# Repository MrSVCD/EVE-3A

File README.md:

# EVE-3A
EVE-3A is a project to make a ADM-3A compatible terminal in a keyboard.

So far MrSVCD has competed a first draft of a Ortholinear and a ADM-3A (Original Layout) inspired keyboard layout.

## Keyboard
### Ortholinear
Renders of the first draft

### ADM-3A inspired (Original Layout)
Renders of the first draft

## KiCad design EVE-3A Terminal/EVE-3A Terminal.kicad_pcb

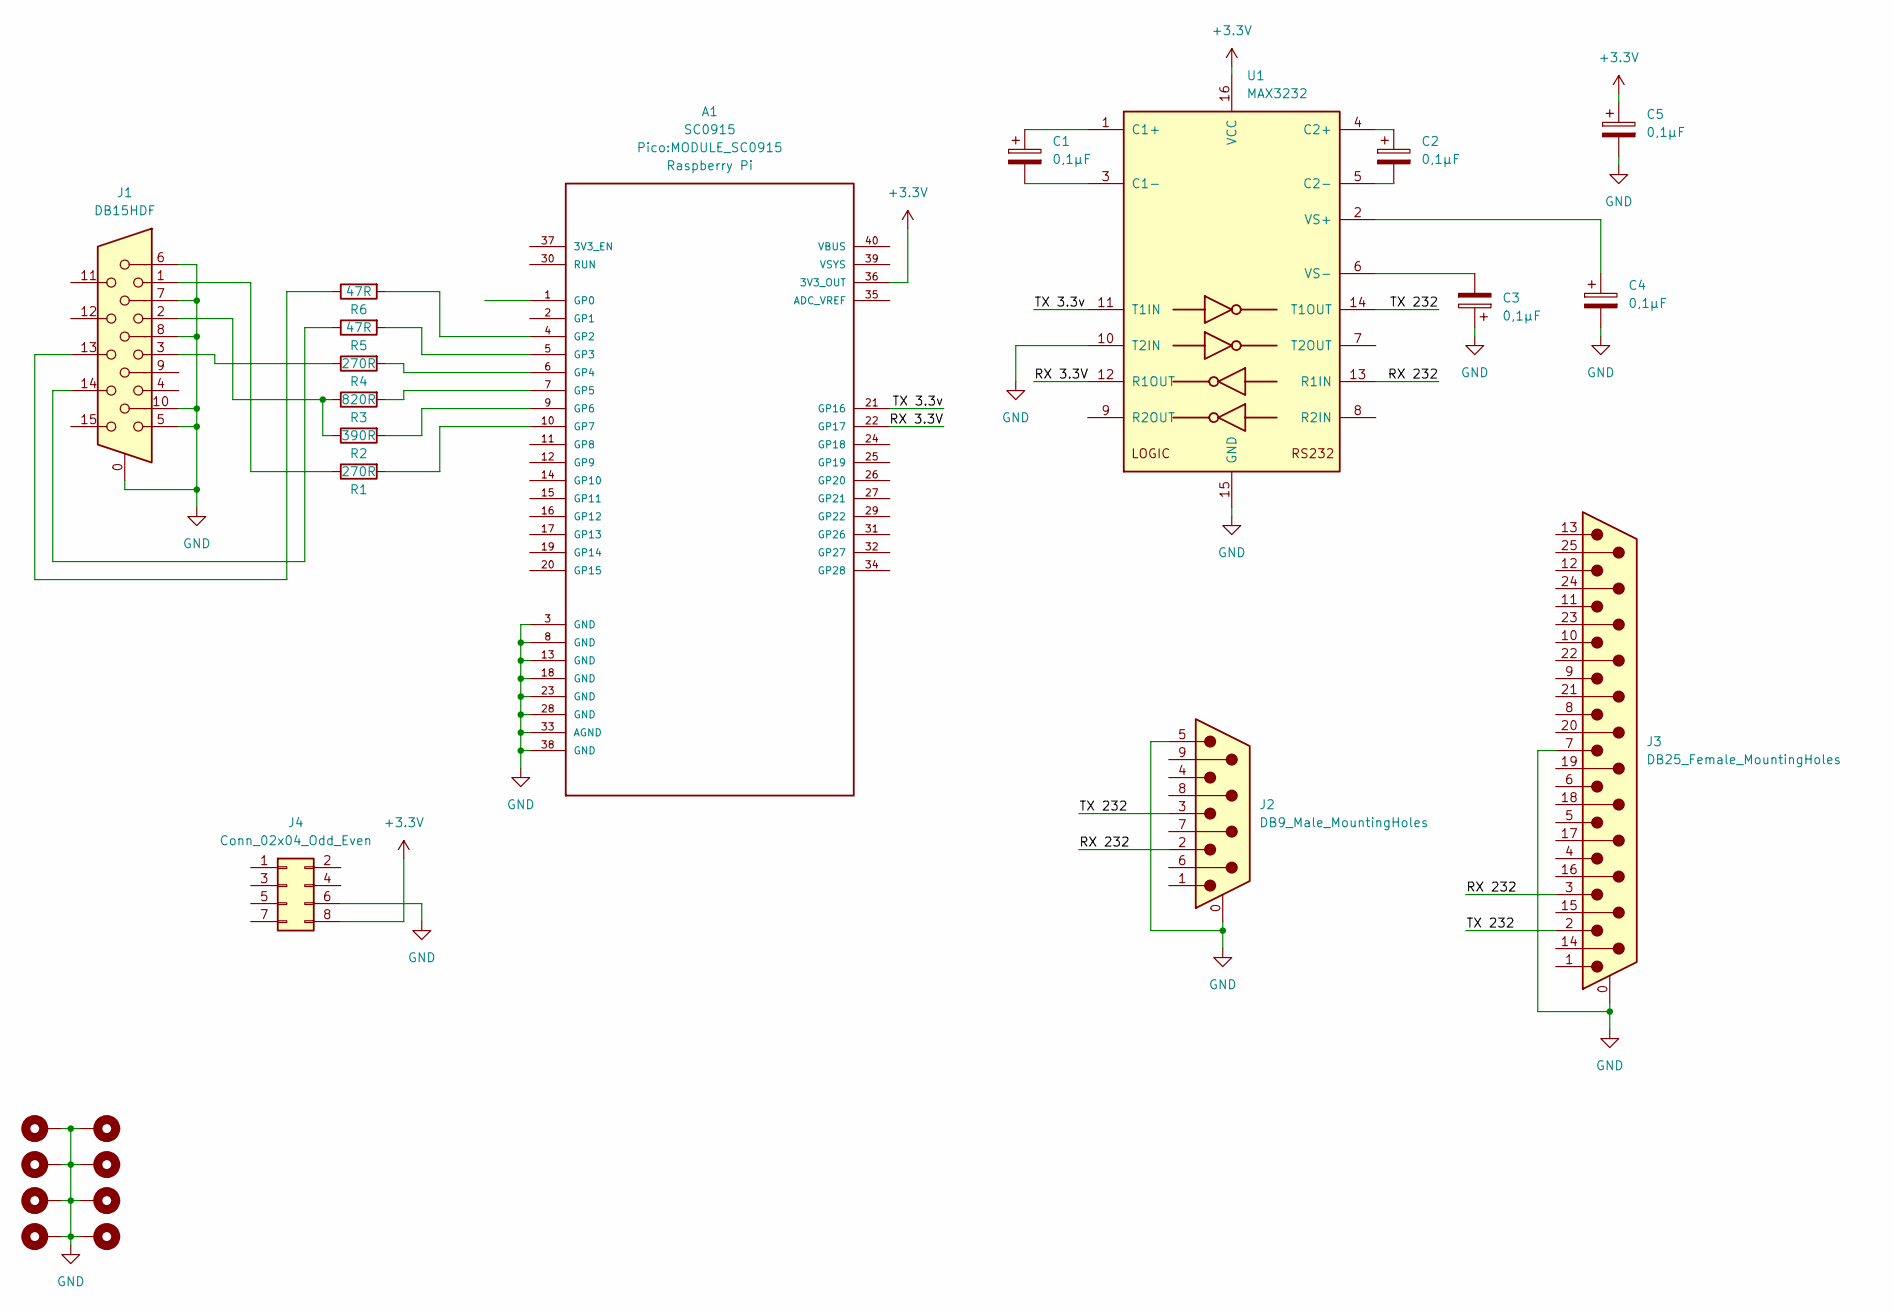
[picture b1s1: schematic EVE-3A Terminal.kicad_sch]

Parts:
A1: SC0915; MODULE_SC0915; PARTREV 1.6
C1, C2, C3, C4, C5: 0,1µF; CP_Radial_D5.0mm_P2.50mm
H1, H2, H3, H4, H5, H6, H7, H8: MountingHole_Pad; MountingHole_3.2mm_M3_Pad_Via
J1: DB15HDF; DSUB-15-HD_Female_Horizontal_P2.29x1.98mm_EdgePinOffset3.03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
J2: DB9_Male_MountingHoles; DSUB-9_Male_Horizontal_P2.77x2.84mm_EdgePinOffset4.94mm_Hou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
J3: DB25_Female_MountingHoles; DSUB-25_Male_Horizontal_P2.77x2.84mm_EdgePinOffset4.94mm_Ho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
J4: Conn_02x04_Odd_Even; PinSocket_2x04_P2.54mm_Vertical
R1, R4: 270R; R_Axial_DIN0207_L6.3mm_D2.5mm_P7.62mm_Horizontal
R2: 390R; R_Axial_DIN0207_L6.3mm_D2.5mm_P7.62mm_Horizontal
R3: 820R; R_Axial_DIN0207_L6.3mm_D2.5mm_P7.62mm_Horizontal
R5, R6: 47R; R_Axial_DIN0207_L6.3mm_D2.5mm_P7.62mm_Horizontal
U1: MAX3232; DIP-16_W7.62mm_Socket_LongPads

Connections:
+3.3V: A1.36 (3V3_OUT), C5.1, J4.8, U1.16 (VCC)
/RX 3.3V: A1.22 (GP17), U1.12 (R1OUT)
/RX 232: J2.2, J3.3, U1.13 (R1IN)
/TX 3.3v: A1.21 (GP16), U1.11 (T1IN)
/TX 232: J2.3, J3.2, U1.14 (T1OUT)
GND: A1.3 (GND), A1.8 (GND), A1.13 (GND), A1.18 (GND), A1.23 (GND), A1.28 (GND), A1.33 (AGND), A1.38 (GND), C3.1, C4.2, C5.2, H1.1, H2.1, H3.1, H4.1, H5.1, H6.1, H7.1, H8.1, J1.0, J1.5, J1.6, J1.7, J1.8, J1.10, J2.0 (PAD), J2.5, J3.0 (PAD), J3.7, J4.6, U1.10 (T2IN), U1.15 (GND)
unnamed: A1.4 (GP2), R6.2
unnamed: A1.5 (GP3), R5.2
unnamed: A1.6 (GP4), R4.2
unnamed: A1.7 (GP5), R3.2
unnamed: A1.9 (GP6), R2.2
unnamed: A1.10 (GP7), R1.2
unnamed: C1.1, U1.1 (C1+)
unnamed: C1.2, U1.3 (C1-)
unnamed: C2.1, U1.4 (C2+)
unnamed: C2.2, U1.5 (C2-)
unnamed: C3.2, U1.6 (VS-)
unnamed: C4.1, U1.2 (VS+)
unnamed: J1.1, R1.1
unnamed: J1.2, R2.1, R3.1
unnamed: J1.3, R4.1
unnamed: J1.13, R6.1
unnamed: J1.14, R5.1

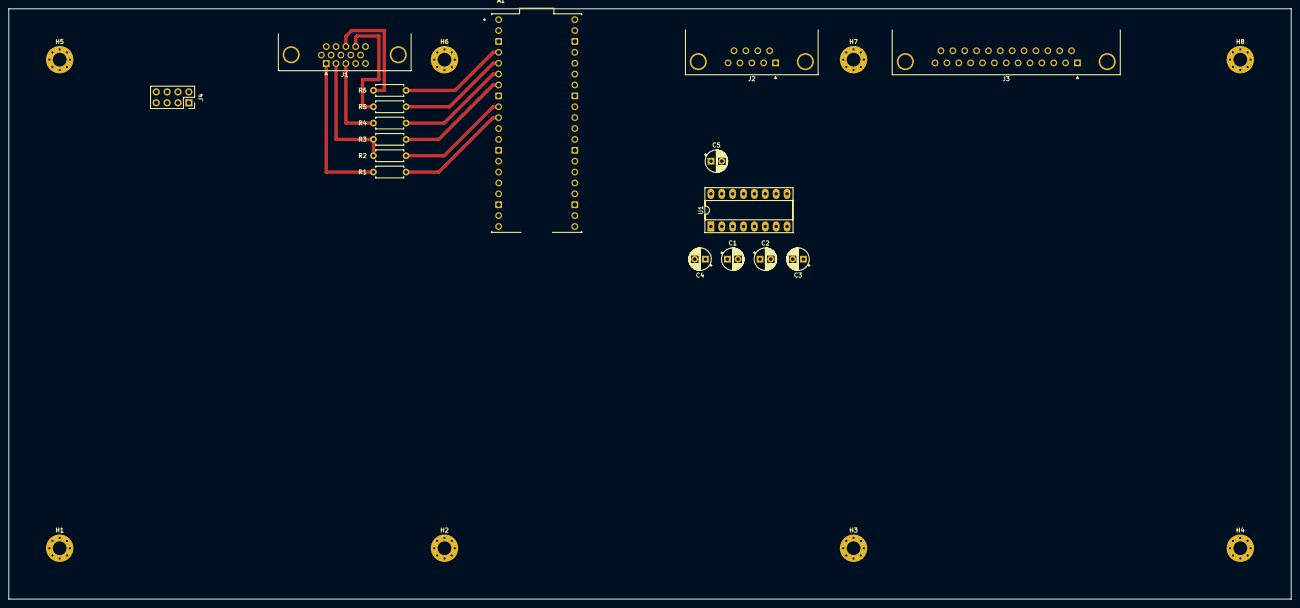
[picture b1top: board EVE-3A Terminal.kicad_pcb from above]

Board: 2 copper layers, 299.2 x 137.8 mm, 25 parts (0 on the bottom side), 23 nets.

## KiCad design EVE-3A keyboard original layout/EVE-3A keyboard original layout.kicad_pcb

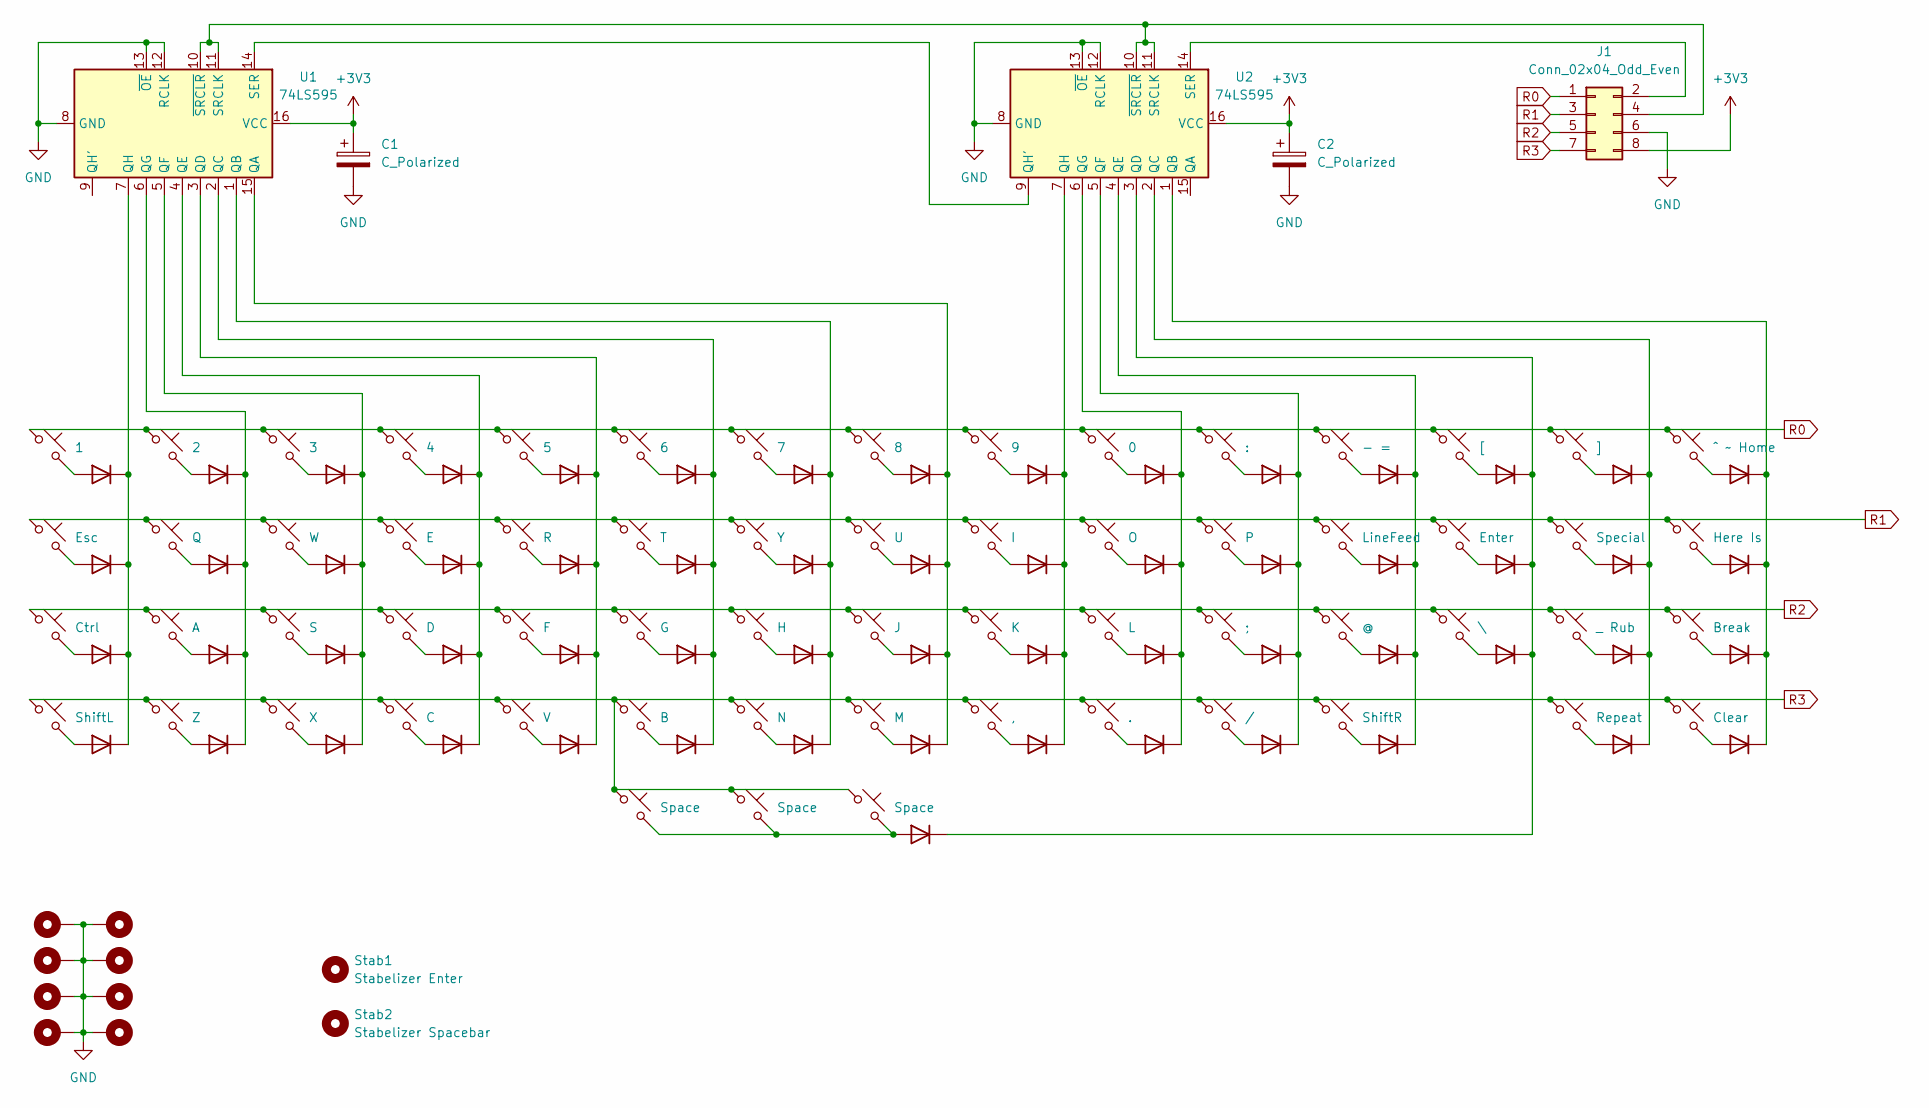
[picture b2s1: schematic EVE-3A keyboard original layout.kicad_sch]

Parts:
C1, C2: C_Polarized; CP_Radial_D7.5mm_P2.50mm
D1, D2, D3, D4, D5, D6, D7, D8, D9, D10, D11, D12, D13, D14, D15, D16, D17, D18, D19, D20, D21, D22, D23, D24, D25, D26, D27, D28, D29, D30, D31, D32, D33, D34, D35, D36, D37, D38, D39, D40, D41, D42, D43, D44, D45, D46, D47, D48, D49, D50, D51, D52, D53, D54, D55, D56, D57, D58, D59, D60: 1N4148; D_DO-35_SOD27_P7.62mm_Horizontal
H1, H2, H3, H4, H5, H6, H7, H8: MountingHole_Pad; MountingHole_3.2mm_M3_Pad_Via
J1: Conn_02x04_Odd_Even; IDC-Header_2x04_P2.54mm_Vertical
SW1: 1; SW_Hybrid_Cherry_MX_Alps_1.00u
SW2: Esc; SW_Hybrid_Cherry_MX_Alps_1.00u
SW3: Ctrl; SW_Hybrid_Cherry_MX_Alps_1.00u
SW4: ShiftL; SW_Hybrid_Cherry_MX_Alps_1.50u
SW5: 2; SW_Hybrid_Cherry_MX_Alps_1.00u
SW6: Q; SW_Hybrid_Cherry_MX_Alps_1.00u
SW7: A; SW_Hybrid_Cherry_MX_Alps_1.00u
SW8: Z; SW_Hybrid_Cherry_MX_Alps_1.00u
SW9: 3; SW_Hybrid_Cherry_MX_Alps_1.00u
SW10: W; SW_Hybrid_Cherry_MX_Alps_1.00u
SW11: S; SW_Hybrid_Cherry_MX_Alps_1.00u
SW12: X; SW_Hybrid_Cherry_MX_Alps_1.00u
SW13: 4; SW_Hybrid_Cherry_MX_Alps_1.00u
SW14: E; SW_Hybrid_Cherry_MX_Alps_1.00u
SW15: D; SW_Hybrid_Cherry_MX_Alps_1.00u
SW16: C; SW_Hybrid_Cherry_MX_Alps_1.00u
SW17: 5; SW_Hybrid_Cherry_MX_Alps_1.00u
SW18: R; SW_Hybrid_Cherry_MX_Alps_1.00u
SW19: F; SW_Hybrid_Cherry_MX_Alps_1.00u
SW20: V; SW_Hybrid_Cherry_MX_Alps_1.00u
SW21: 6; SW_Hybrid_Cherry_MX_Alps_1.00u
SW22: T; SW_Hybrid_Cherry_MX_Alps_1.00u
SW23: G; SW_Hybrid_Cherry_MX_Alps_1.00u
SW24: B; SW_Hybrid_Cherry_MX_Alps_1.00u
SW25, SW35: Space; SW_Hybrid_Cherry_MX_Alps_1.50u
SW26: 7; SW_Hybrid_Cherry_MX_Alps_1.00u
SW27: Y; SW_Hybrid_Cherry_MX_Alps_1.00u
SW28: H; SW_Hybrid_Cherry_MX_Alps_1.00u
SW29: N; SW_Hybrid_Cherry_MX_Alps_1.00u
SW30: Space; SW_Hybrid_Cherry_MX_Alps_6.50u
SW31: 8; SW_Hybrid_Cherry_MX_Alps_1.00u
SW32: U; SW_Hybrid_Cherry_MX_Alps_1.00u
SW33: J; SW_Hybrid_Cherry_MX_Alps_1.00u
SW34: M; SW_Hybrid_Cherry_MX_Alps_1.00u
SW36: 9; SW_Hybrid_Cherry_MX_Alps_1.00u
SW37: I; SW_Hybrid_Cherry_MX_Alps_1.00u
SW38: K; SW_Hybrid_Cherry_MX_Alps_1.00u
SW39: ,; SW_Hybrid_Cherry_MX_Alps_1.00u
SW40: 0; SW_Hybrid_Cherry_MX_Alps_1.00u
SW41: O; SW_Hybrid_Cherry_MX_Alps_1.00u
SW42: L; SW_Hybrid_Cherry_MX_Alps_1.00u
SW43: .; SW_Hybrid_Cherry_MX_Alps_1.00u
SW44: :; SW_Hybrid_Cherry_MX_Alps_1.00u
SW45: P; SW_Hybrid_Cherry_MX_Alps_1.00u
SW46: ;; SW_Hybrid_Cherry_MX_Alps_1.00u
SW47: /; SW_Hybrid_Cherry_MX_Alps_1.00u
SW48: - =; SW_Hybrid_Cherry_MX_Alps_1.00u
SW49: LineFeed; SW_Hybrid_Cherry_MX_Alps_1.00u
SW50: @; SW_Hybrid_Cherry_MX_Alps_1.00u
SW51: ShiftR; SW_Hybrid_Cherry_MX_Alps_1.50u
SW52: [; SW_Hybrid_Cherry_MX_Alps_1.00u
SW53: Enter; SW_Hybrid_Cherry_MX_Alps_2.00u
SW54: \; SW_Hybrid_Cherry_MX_Alps_1.00u
SW55: ]; SW_Hybrid_Cherry_MX_Alps_1.00u
SW56: _ Rub; SW_Hybrid_Cherry_MX_Alps_1.00u
SW57: Repeat; SW_Hybrid_Cherry_MX_Alps_1.00u
SW58: ^ ~ Home; SW_Hybrid_Cherry_MX_Alps_1.00u
SW59: Here Is; SW_Hybrid_Cherry_MX_Alps_1.00u
SW60: Break; SW_Hybrid_Cherry_MX_Alps_1.00u
SW61: Clear; SW_Hybrid_Cherry_MX_Alps_1.00u
SW62: Special; SW_PUSH-12mm
Stab1: Stabelizer Enter; Stabilizer_Cherry_MX_2.00u
Stab2: Stabelizer Spacebar; Stabilizer_Cherry_MX_6.00u
U1, U2: 74LS595; DIP-16_W7.62mm_Socket

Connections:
+3V3: C1.1, C2.1, J1.8, U1.16 (VCC), U2.16 (VCC)
GND: C1.2, C2.2, H1.1, H2.1, H3.1, H4.1, H5.1, H6.1, H7.1, H8.1, J1.6, U1.8 (GND), U1.12 (RCLK), U1.13 (~OE), U2.8 (GND), U2.12 (RCLK), U2.13 (~OE)
unnamed: D1.1 (K), D2.1 (K), D3.1 (K), D4.1 (K), U1.7 (QH)
unnamed: D1.2 (A), SW1.1
unnamed: D2.2 (A), SW2.1
unnamed: D3.2 (A), SW3.1
unnamed: D4.2 (A), SW4.1
unnamed: D5.1 (K), D6.1 (K), D7.1 (K), D8.1 (K), U1.6 (QG)
unnamed: D5.2 (A), SW5.1
unnamed: D6.2 (A), SW6.1
unnamed: D7.2 (A), SW7.1
unnamed: D8.2 (A), SW8.1
unnamed: D9.2 (A), SW9.1
unnamed: D9.1 (K), D10.1 (K), D11.1 (K), D12.1 (K), U1.5 (QF)
unnamed: D10.2 (A), SW10.1
unnamed: D11.2 (A), SW11.1
unnamed: D12.2 (A), SW12.1
unnamed: D13.1 (K), D14.1 (K), D15.1 (K), D16.1 (K), U1.4 (QE)
unnamed: D13.2 (A), SW13.1
unnamed: D14.2 (A), SW14.1
unnamed: D15.2 (A), SW15.1
unnamed: D16.2 (A), SW16.1
unnamed: D17.1 (K), D18.1 (K), D19.1 (K), D20.1 (K), U1.3 (QD)
unnamed: D17.2 (A), SW17.1
unnamed: D18.2 (A), SW18.1
unnamed: D19.2 (A), SW19.1
unnamed: D20.2 (A), SW20.1
unnamed: D21.1 (K), D22.1 (K), D23.1 (K), D24.1 (K), U1.2 (QC)
unnamed: D21.2 (A), SW21.1
unnamed: D22.2 (A), SW22.1
unnamed: D23.2 (A), SW23.1
unnamed: D24.2 (A), SW24.1
unnamed: D25.1 (K), D26.1 (K), D27.1 (K), D28.1 (K), U1.1 (QB)
unnamed: D25.2 (A), SW26.1
unnamed: D26.2 (A), SW27.1
unnamed: D27.2 (A), SW28.1
unnamed: D28.2 (A), SW29.1
unnamed: D29.1 (K), D30.1 (K), D31.1 (K), D32.1 (K), U1.15 (QA)
unnamed: D29.2 (A), SW31.1
unnamed: D30.2 (A), SW32.1
unnamed: D31.2 (A), SW33.1
unnamed: D32.2 (A), SW34.1
unnamed: D33.1 (K), D50.1 (K), D51.1 (K), D52.1 (K), U2.3 (QD)
unnamed: D33.2 (A), SW25.1, SW30.1, SW35.1
unnamed: D34.1 (K), D35.1 (K), D36.1 (K), D37.1 (K), U2.7 (QH)
unnamed: D34.2 (A), SW36.1
unnamed: D35.2 (A), SW37.1
unnamed: D36.2 (A), SW38.1
unnamed: D37.2 (A), SW39.1
unnamed: D38.1 (K), D39.1 (K), D40.1 (K), D41.1 (K), U2.6 (QG)
unnamed: D38.2 (A), SW40.1
unnamed: D39.2 (A), SW41.1
unnamed: D40.2 (A), SW42.1
unnamed: D41.2 (A), SW43.1
unnamed: D42.1 (K), D43.1 (K), D44.1 (K), D45.1 (K), U2.5 (QF)
unnamed: D42.2 (A), SW44.1
unnamed: D43.2 (A), SW45.1
unnamed: D44.2 (A), SW46.1
unnamed: D45.2 (A), SW47.1
unnamed: D46.1 (K), D47.1 (K), D48.1 (K), D49.1 (K), U2.4 (QE)
unnamed: D46.2 (A), SW48.1
unnamed: D47.2 (A), SW49.1
unnamed: D48.2 (A), SW50.1
unnamed: D49.2 (A), SW51.1
unnamed: D50.2 (A), SW52.1
unnamed: D51.2 (A), SW53.1
unnamed: D52.2 (A), SW54.1
unnamed: D53.1 (K), D54.1 (K), D55.1 (K), D60.1 (K), U2.2 (QC)
unnamed: D53.2 (A), SW55.1
unnamed: D54.2 (A), SW56.1
unnamed: D55.2 (A), SW57.1
unnamed: D56.1 (K), D57.1 (K), D58.1 (K), D59.1 (K), U2.1 (QB)
unnamed: D56.2 (A), SW58.1
unnamed: D57.2 (A), SW59.1
unnamed: D58.2 (A), SW60.1
unnamed: D59.2 (A), SW61.1
unnamed: D60.2 (A), SW62.1
unnamed: J1.2, U2.14 (SER)
unnamed: J1.4, U1.10 (~SRCLR), U1.11 (SRCLK), U2.10 (~SRCLR), U2.11 (SRCLK)
unnamed: U1.14 (SER), U2.9 (QH')
R0: J1.1, SW1.2, SW5.2, SW9.2, SW13.2, SW17.2, SW21.2, SW26.2, SW31.2, SW36.2, SW40.2, SW44.2, SW48.2, SW52.2, SW55.2, SW58.2
R1: J1.3, SW2.2, SW6.2, SW10.2, SW14.2, SW18.2, SW22.2, SW27.2, SW32.2, SW37.2, SW41.2, SW45.2, SW49.2, SW53.2, SW59.2, SW62.2
R2: J1.5, SW3.2, SW7.2, SW11.2, SW15.2, SW19.2, SW23.2, SW28.2, SW33.2, SW38.2, SW42.2, SW46.2, SW50.2, SW54.2, SW56.2, SW60.2
R3: J1.7, SW4.2, SW8.2, SW12.2, SW16.2, SW20.2, SW24.2, SW25.2, SW29.2, SW30.2, SW34.2, SW35.2, SW39.2, SW43.2, SW47.2, SW51.2, SW57.2, SW61.2

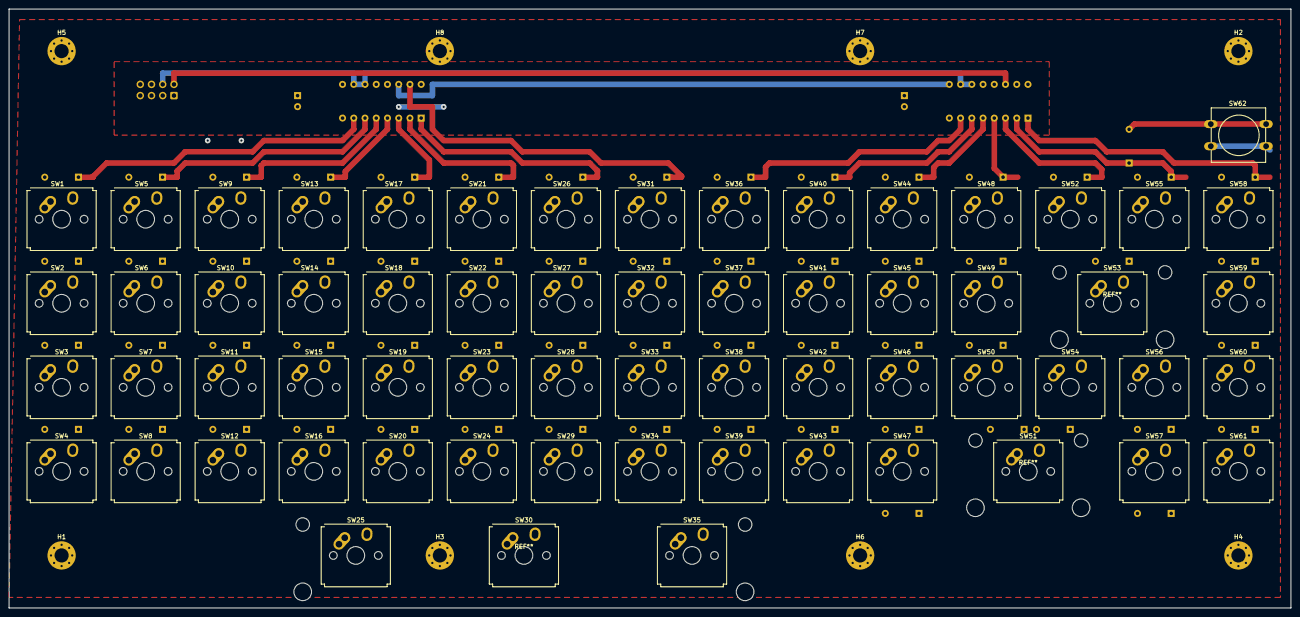
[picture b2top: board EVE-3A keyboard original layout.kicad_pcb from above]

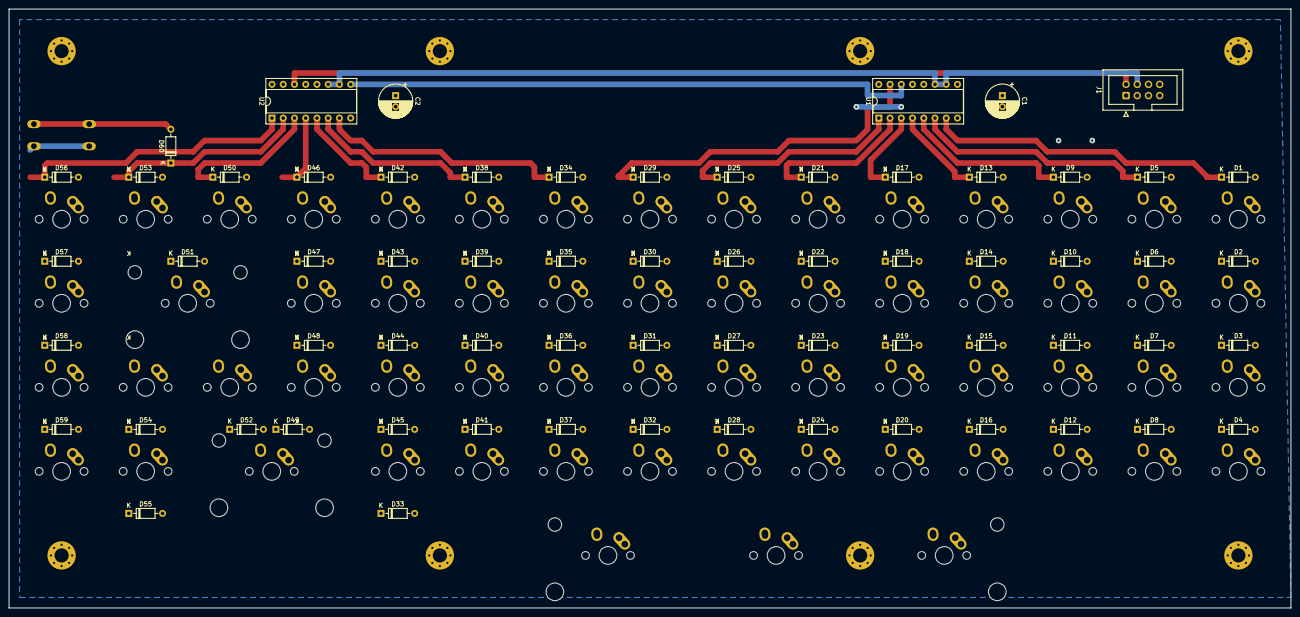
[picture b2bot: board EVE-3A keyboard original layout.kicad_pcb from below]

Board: 2 copper layers, 289.8 x 135.4 mm, 135 parts (65 on the bottom side), 84 nets.

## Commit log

2022-07-09 filling the repo
2022-07-09 interim checkin
2022-07-10 Completed first draft of Ortholinear layout. Removed old layout that is not up to date with new schematics.
2022-07-10 Set License to GNU GPL 3
2022-07-10 Removed backup folder
2022-07-10 Original Layout branch added
2022-07-10 trying new .gitignore
2022-07-10 The new .gitignore worked.
2022-07-12 First draft of Original Layout
2022-07-12 Added renders of the PCBs
2022-07-15 Renaming files and Cleanup
2022-07-15 Renaming files and Cleanup, again
